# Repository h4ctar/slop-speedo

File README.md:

# slop-speedo

A custom digital speedometer/clock gauge for a motorcycle, replacing the stock
analog instrument: an X27.168 air-core stepper drives the needle, a small
OLED shows the display functions, and one MODE button drives the whole UI.
Built on an STM32F103C8T6 ("Blue Pill" class), a custom KiCad PCB, and a
hall-effect sensor off the stock speedo drive on the front wheel.

## Repo layout

- `firmware/` — STM32CubeMX + HAL project (CMake). Hand-written application
  code in `firmware/app/`; architecture in [`firmware/DESIGN.md`](firmware/DESIGN.md);
  style in [`firmware/CODE_STYLE.md`](firmware/CODE_STYLE.md).
- `hardware/` — KiCad 10 PCB project (revision 1, built and working). Generated
  outputs land in `hardware/generated/` and `hardware/JLCPCB/` via CI.

## Features

Working:

- Needle homing and positioning (X27.168, 960 steps full scale, 1.2 ms/step)
- OLED functions cycled by short MODE presses, each introduced by its name
- CLOCK: live time, long press enters set mode (set hours/minutes by button);
  the set time survives resets
- VOLT: battery voltage from the on-board divider (PA7)

In progress:

- SPEED: needle + display from the stock speedo drive (hall sensor on order);
  km/h <-> mi/h toggle
- ODOMETER / TRIP: distance from the wheel pulses; odometer persisted in
  flash, trip reset by long press

## The board

- STM32F103C8T6 (LQFP48), HSE 16 MHz, RTC on the 32.768 kHz LSE
  crystal (kept running by the J5 Vbat battery)
- Connectors: J1 debug (SWD + 3.3V), J2 mode button, J3 speedo sensor,
  J4 power (12 V -> buck 5 V -> LDO 3.3 V), J5 VBAT (backup battery),
  J7 breakout (3.3V / PA8-PA12 / GND)

## Building the firmware

Needs `arm-none-eabi-gcc`, `arm-none-eabi-newlib` (for `nano.specs`) and
`ninja` (Arch: `pacman -S arm-none-eabi-gcc arm-none-eabi-newlib ninja`).

```sh
cd firmware
cmake --preset Debug && cmake --build --preset Debug   # or Release
```

`firmware/check.sh` runs a strict (`-Werror`) build of both presets — the
same thing CI does. Output: `build/<preset>/speedo-code.elf`.

## Flashing

With an ST-Link attached:

```sh
firmware/flash.sh [Debug|Release]   # OpenOCD; defaults to Debug
```

## Using the gauge

- **Short press** cycles the display functions: SPEED -> CLOCK -> VOLT ->
  ODO -> TRIP (each function's name flashes for a second first)
- **Long press** is the current function's action: CLOCK enters set mode
  (short presses increment, long presses advance hours -> minutes -> done),
  SPEED switches km/h <-> mi/h, TRIP resets (planned)

## Development process

Work items and status live in [`TODO.md`](TODO.md). Firmware changes are
verified with `check.sh`, reviewed by the `firmware-reviewer` and
`style-reviewer` agents, and hardware-tested before being committed. CI
builds the firmware and runs KiBot (ERC/DRC + outputs) on every push.

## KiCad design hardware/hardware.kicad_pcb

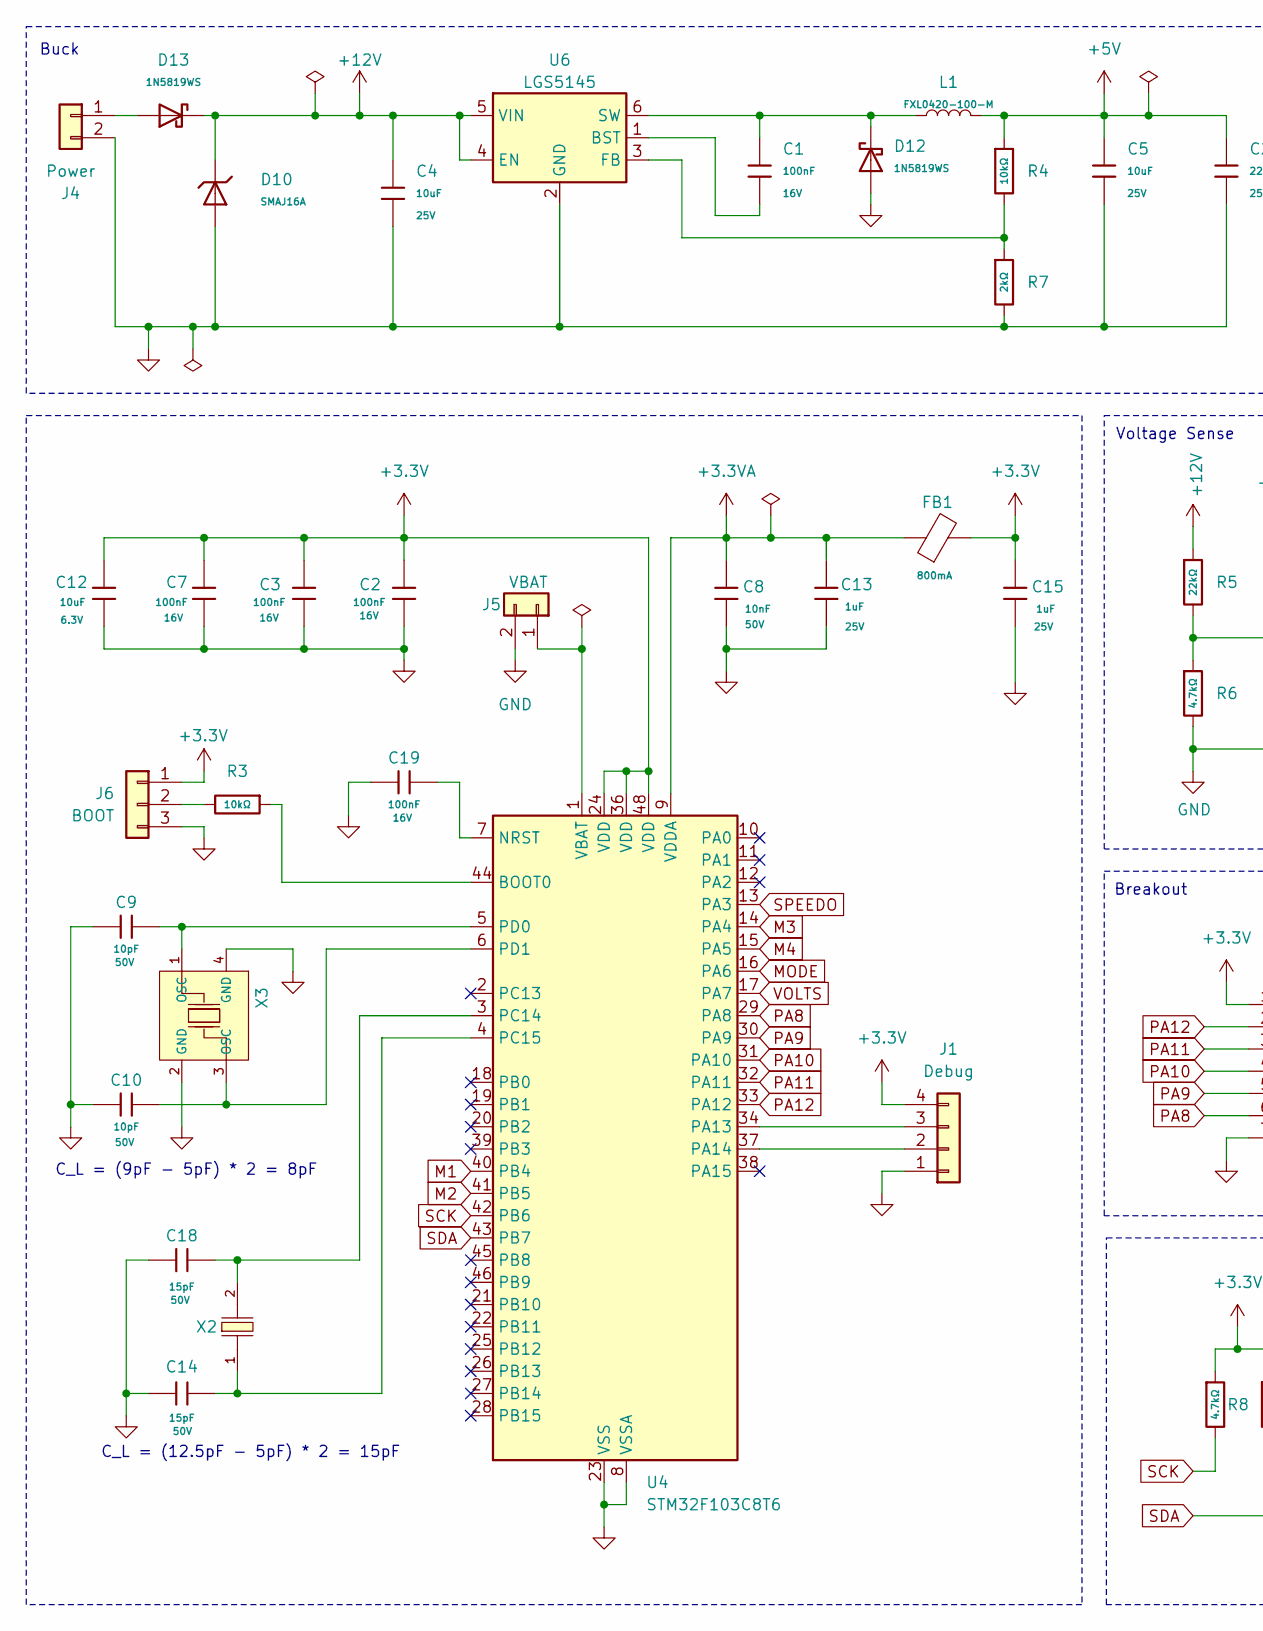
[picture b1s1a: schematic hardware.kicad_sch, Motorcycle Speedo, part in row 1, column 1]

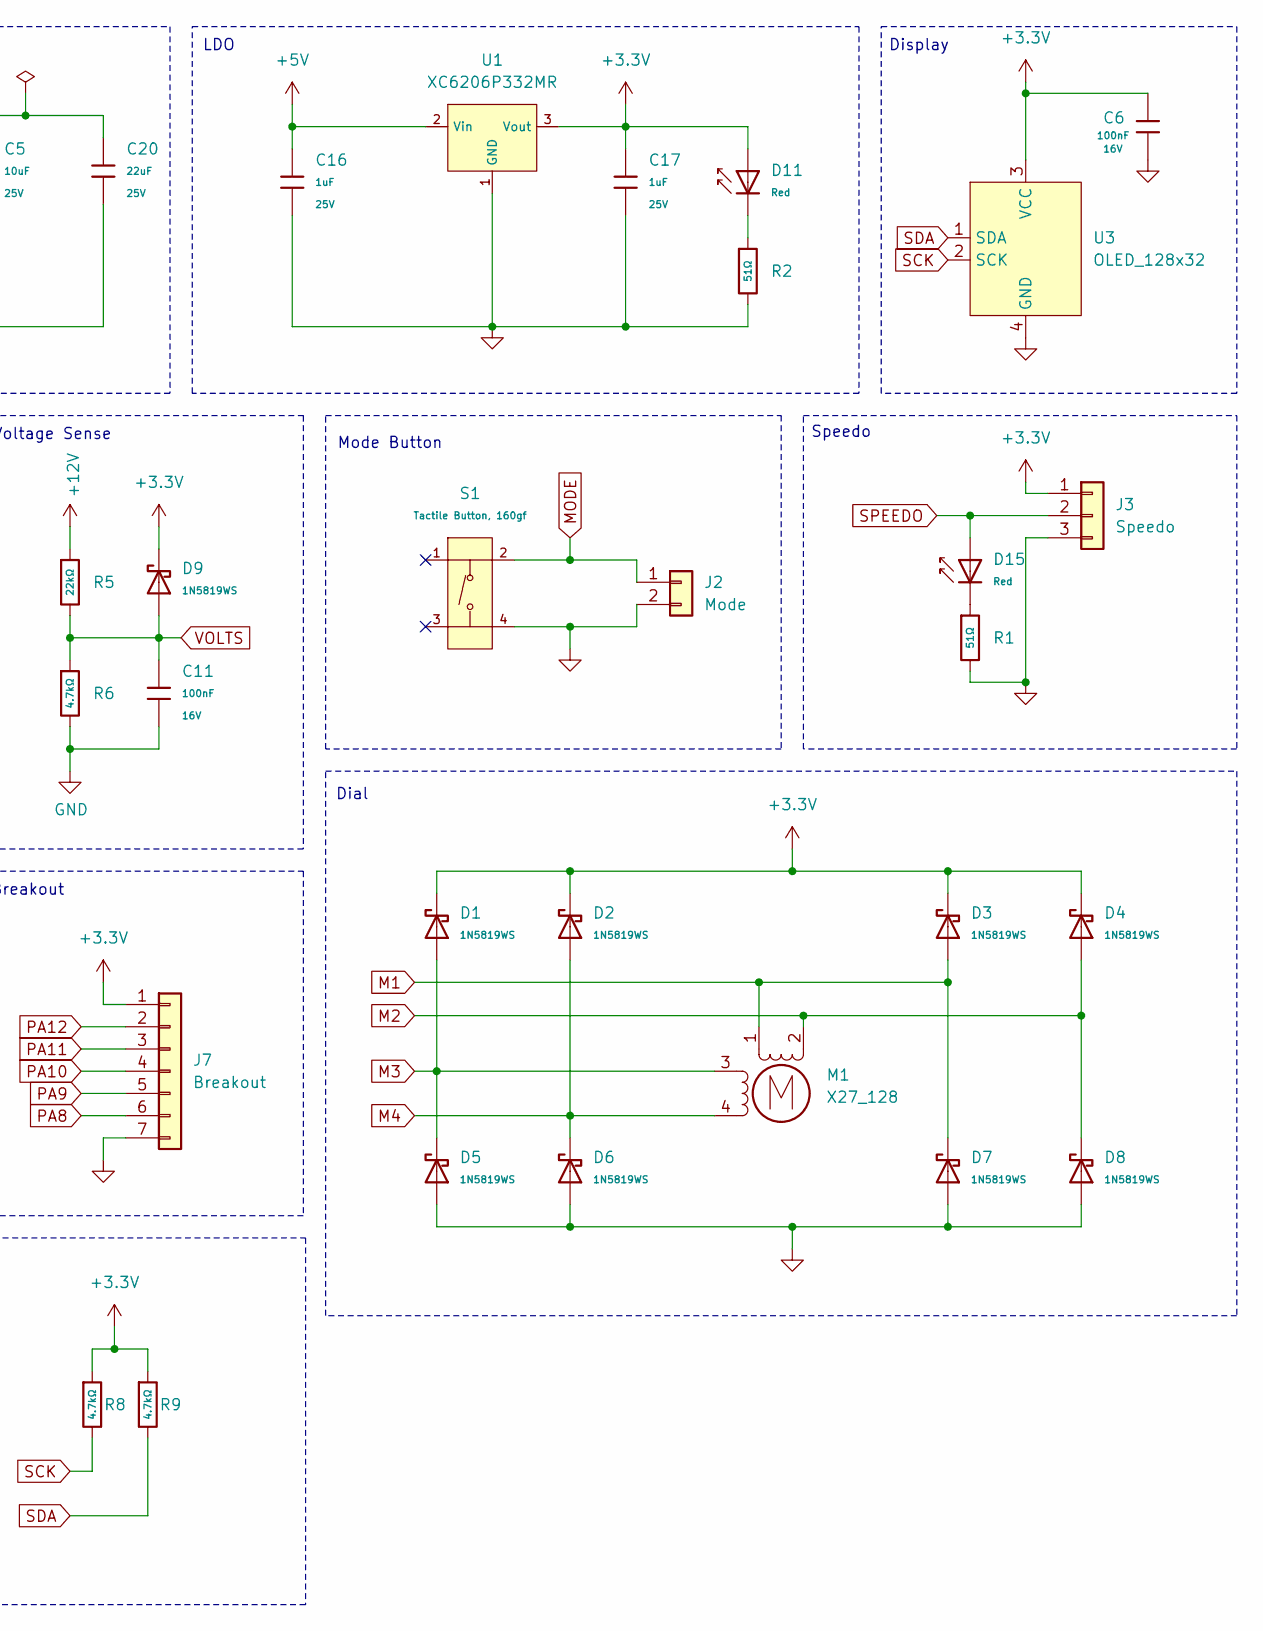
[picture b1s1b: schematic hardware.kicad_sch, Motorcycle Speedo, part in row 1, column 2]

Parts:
C1, C2, C3, C6, C7, C11, C19: 100nF; C_0402; Voltage Rated 16V; Tolerance ±10%; Part CL05B104KO5NNNC; LCSC C1525
C4, C5: 10uF; C_0805; Voltage Rated 25V; Tolerance ±10%; Part CL21A106KAYNNNE; LCSC C15850
C8: 10nF; C_0402; Voltage Rated 50V; Tolerance ±10%; Part CL05B103KB5NNNC; LCSC C15195
C9, C10: 10pF; C_0402; Voltage Rated 50V; Tolerance ±5%; Part CL05C100JB5NNNC; LCSC C32949
C12: 10uF; C_0402; Voltage Rated 6.3V; Tolerance ±20%; Part CL05A106MQ5NUNC; LCSC C15525
C13, C15, C16, C17: 1uF; C_0402; Voltage Rated 25V; Tolerance ±10%; Part CL05A105KA5NQNC; LCSC C52923
C14, C18: 15pF; C_0402; Voltage Rated 50V; Tolerance ±5%; Part 0402CG150J500NT; LCSC C1548
C20: 22uF; C_0805; Voltage Rated 25V; Tolerance ±20%; Part CL21A226MAQNNNE; LCSC C45783
D1, D2, D3, D4, D5, D6, D7, D8, D9, D12, D13: 1N5819WS; D_SOD-323; Forward Voltage (Vf@If) 600mV@1A; Reverse Voltage (Vr) 40V; Part 1N5819WS; LCSC C191023
D10: SMAJ16A; D_SMA; Breakdown Voltage 19.7V; Part SMAJ16A; LCSC C41376405
D11, D15: Red; D_0603; Part KT-0603R; LCSC C2286
FB1: FB_0805; Current Rating 800mA; Tolerance ±25%; Part GZ2012D101TF; LCSC C1015
J1: Debug; PinHeader_1x04_P2.54mm_Vertical
J2: Mode; JST_PH_B2B-PH-K_1x02_P2.00mm_Vertical
J3: Speedo; JST_PH_B3B-PH-K_1x03_P2.00mm_Vertical
J4: Power; JST_PH_B2B-PH-K_1x02_P2.00mm_Vertical
J5: VBAT; JST_PH_B2B-PH-K_1x02_P2.00mm_Vertical
J6: BOOT; PinHeader_1x03_P2.54mm_Vertical
J7: Breakout; PinSocket_1x07_P2.54mm_Vertical
L1: FXL0420-100-M; L_Sunlord_MWSA0402S; LCSC C177242
M1: X27_128; X27_168
R1, R2: 51Ω; R_0402; Overload Voltage (Max) 50V; Tolerance ±1%; Part 0402WGF510JTCE; LCSC C25125
R3, R4: 10kΩ; R_0402; Overload Voltage (Max) 50V; Tolerance ±1%; Part 0402WGF1002TCE; LCSC C25744
R5: 22kΩ; R_0402; Overload Voltage (Max) 50V; Tolerance ±1%; Part 0402WGF2202TCE; LCSC C25768
R6, R8, R9: 4.7kΩ; R_0402; Overload Voltage (Max) 50V; Tolerance ±1%; Part 0402WGF4701TCE; LCSC C25900
R7: 2kΩ; R_0402; Overload Voltage (Max) 50V; Tolerance ±1%; Part 0402WGF2001TCE; LCSC C4109
S1: Tactile Button, 160gf; SW-SMD_4P-L5.1-W5.1-P3.70-LS6.5-TL-2; Voltage Rating (Dc) 12V; Part TS-1187A-B-A-B; LCSC C318884
U1: XC6206P332MR; SOT-23-3_L2.9-W1.6-P1.90-LS2.8-BR; Output Voltage 3.3V; Dropout Voltage 680mV@(100mA); Part XC6206P332MR-G; LCSC C5446
U3: OLED_128x32; OLED_128_32
U4: STM32F103C8T6; LQFP-48_7x7mm_P0.5mm; Operating Voltage Range 2V~3.6V; Low Voltage Detection T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 2V~3.6V; Part STM32F103C8T6; LCSC C8734
U6: LGS5145; SOT-23-6; LCSC C5123971
X2: Q13FC1350000400; FC-135R_L3.2-W1.5; Frequency Tolerance ±20ppm; Part Q13FC13500004; LCSC C32346
X3: X322516MLB4SI; OSC-SMD_4P-L3.2-W2.5-BL; Frequency Tolerance ±10ppm; Part X322516MLB4SI; LCSC C13738

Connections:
+3.3V: C2.1, C3.1, C6.1, C7.1, C12.1, C15.1, C17.1, D1.1, D2.1, D3.1, D4.1, D9.1, D11.2, FB1.2, J1.4, J3.1, J6.1, J7.1, R8.1, R9.1, U1.3 (Vout), U3.3 (VCC), U4.24 (VDD), U4.36 (VDD), U4.48 (VDD)
+3.3VA: C8.1, C13.1, FB1.1, U4.9 (VDDA)
+5V: C5.1, C16.1, C20.1, L1.2, R4.1, U1.2 (Vin)
+12V: C4.1, D10.1, D13.1, R5.1, U6.4 (EN), U6.5 (VIN)
GND: C2.2, C3.2, C4.2, C5.2, C6.2, C7.2, C8.2, C9.1, C10.1, C11.2, C12.2, C13.2, C14.1, C15.2, C16.2, C17.2, C18.1, C19.1, C20.2, D5.2, D6.2, D7.2, D8.2, D10.2, D12.2, J1.1, J2.2, J3.3, J4.2, J5.2, J6.3, J7.7, R1.2, R2.2, R6.2, R7.2, S1.4 (D), U1.1 (GND), U3.4 (GND), U4.8 (VSSA), U4.23 (VSS), U4.35 (VSS), U4.47 (VSS), U6.2 (GND), X3.2 (GND), X3.4 (GND)
M1: D3.2, D7.1, M1.1, U4.40 (PB4)
M2: D4.2, D8.1, M1.2 (-), U4.41 (PB5)
M3: D1.2, D5.1, M1.3, U4.14 (PA4)
M4: D2.2, D6.1, M1.4, U4.15 (PA5)
MODE: J2.1, S1.2 (B), U4.16 (PA6)
unnamed: D11.1, R2.1
unnamed: D15.1, R1.1
unnamed: J1.2, U4.37 (PA14)
unnamed: J1.3, U4.34 (PA13)
unnamed: D13.2, J4.1
unnamed: J5.1, U4.1 (VBAT)
unnamed: J6.2, R3.2
unnamed: R3.1, U4.44 (BOOT0)
unnamed: C19.2, U4.7 (NRST)
unnamed: C18.2, U4.3 (PC14), X2.2
unnamed: C14.2, U4.4 (PC15), X2.1
unnamed: C9.2, U4.5 (PD0), X3.1 (OSC)
unnamed: C10.2, U4.6 (PD1), X3.3 (OSC)
unnamed: C1.1, U6.1 (BST)
unnamed: R4.2, R7.1, U6.3 (FB)
unnamed: C1.2, D12.1, L1.1, U6.6 (SW)
PA8: J7.6, U4.29 (PA8)
PA9: J7.5, U4.30 (PA9)
PA10: J7.4, U4.31 (PA10)
PA11: J7.3, U4.32 (PA11)
PA12: J7.2, U4.33 (PA12)
SCK: R8.2, U3.2 (SCK), U4.42 (PB6)
SDA: R9.2, U3.1 (SDA), U4.43 (PB7)
SPEEDO: D15.2, J3.2, U4.13 (PA3)
VOLTS: C11.1, D9.2, R5.2, R6.1, U4.17 (PA7)

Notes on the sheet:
LDO
Dial
Speedo
C_L = (9pF - 5pF) * 2 = 8pF
C_L = (12.5pF - 5pF) * 2 = 15pF
Display
Buck
Breakout
Mode Button
Voltage Sense

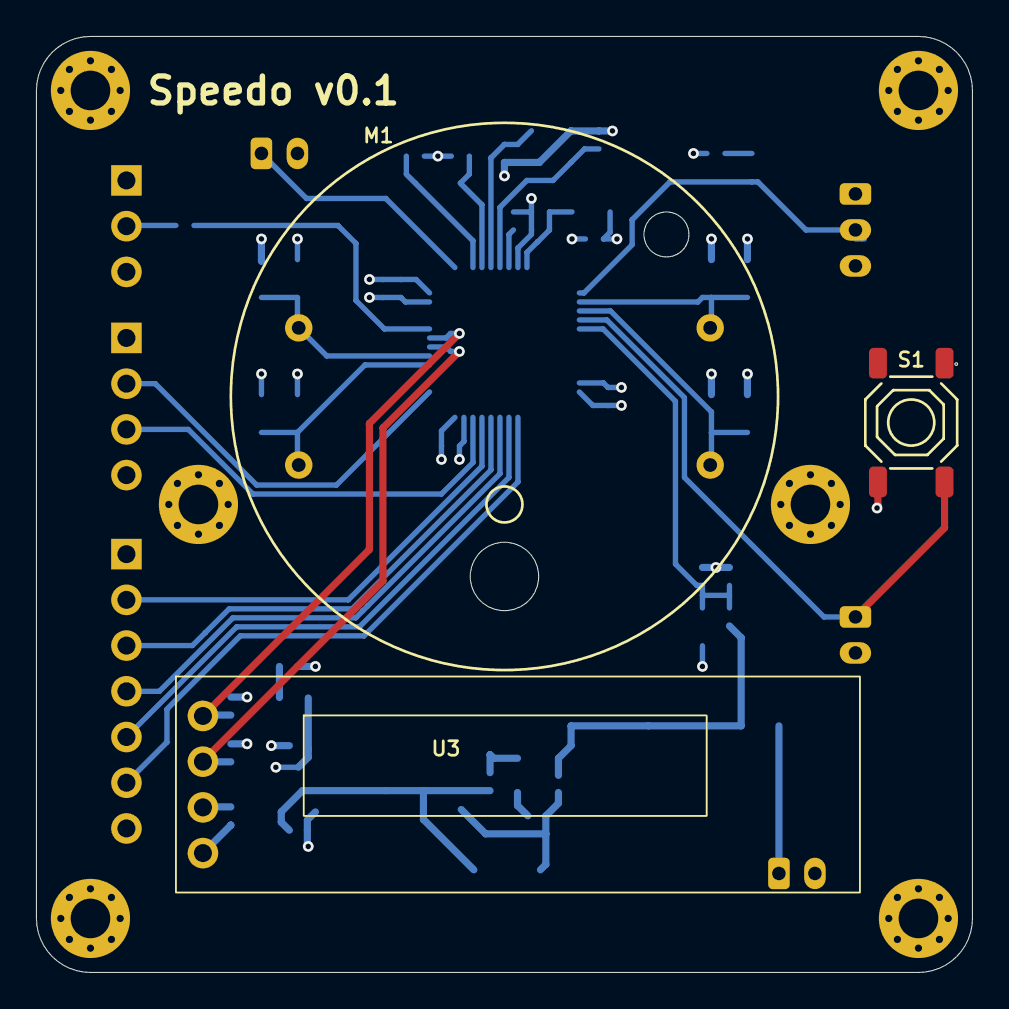
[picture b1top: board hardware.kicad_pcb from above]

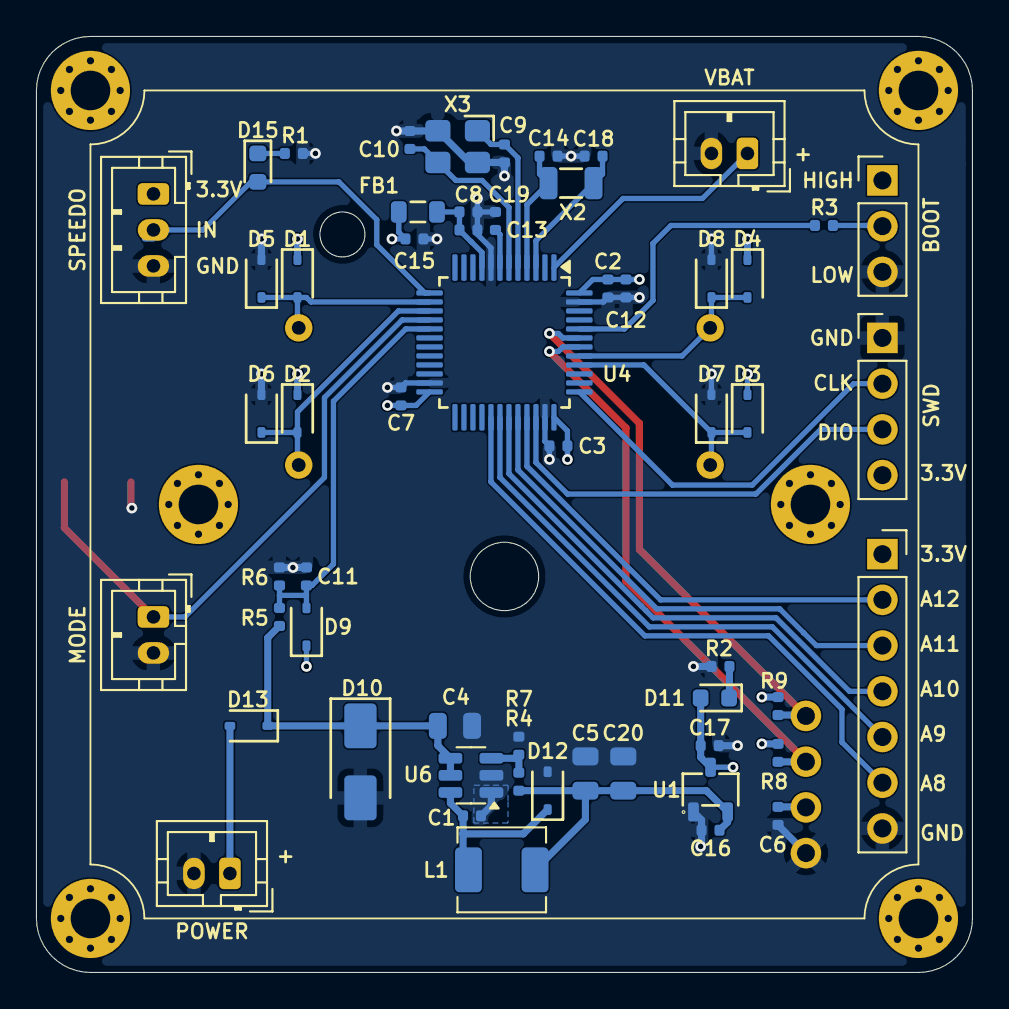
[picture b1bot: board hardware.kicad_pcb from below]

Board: 4 copper layers, 52.0 x 52.0 mm, 66 parts (57 on the bottom side), 35 nets.

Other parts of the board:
H1, H2, H3, H4, H5, H6: MountingHole_2.2mm_M2_Pad_Via

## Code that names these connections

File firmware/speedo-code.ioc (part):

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Mcu.Name=STM32F103C(8-B)Tx
Mcu.Package=LQFP48
Mcu.UserName=STM32F103C8Tx
PA13.Mode=Serial_Wire
PA13.Signal=SYS_JTMS-SWDIO
PA14.Mode=Serial_Wire
PA14.Signal=SYS_JTCK-SWCLK
PA4.GPIOParameters=GPIO_Label
PA4.GPIO_Label=M3
PA4.Signal=GPIO_Output
PA5.GPIOParameters=GPIO_Label
PA5.GPIO_Label=M4
PA5.Signal=GPIO_Output
PA6.GPIOParameters=GPIO_PuPd
PA6.GPIO_PuPd=GPIO_PULLUP
PA6.Signal=GPIO_Input
PA7.GPIOParameters=GPIO_Label
PA7.GPIO_Label=VOLTS
PA7.Signal=ADCx_IN7
PB4.GPIOParameters=GPIO_Label
PB4.GPIO_Label=M1
PB4.Signal=GPIO_Output
PB5.GPIOParameters=GPIO_Label
PB5.GPIO_Label=M2
PB5.Signal=GPIO_Output
PB6.Mode=I2C
PB6.Signal=I2C1_SCL
PB7.Mode=I2C
PB7.Signal=I2C1_SDA
PC14-OSC32_IN.Mode=LSE-External-Oscillator
PC14-OSC32_IN.Signal=RCC_OSC32_IN
PC15-OSC32_OUT.Mode=LSE-External-Oscillator
PC15-OSC32_OUT.Signal=RCC_OSC32_OUT
PD0-OSC_IN.Mode=HSE-External-Oscillator
PD0-OSC_IN.Signal=RCC_OSC_IN
PD1-OSC_OUT.Mode=HSE-External-Oscillator
PD1-OSC_OUT.Signal=RCC_OSC_OUT
RCC.HSE_VALUE=16000000
RCC.SYSCLKFreq_VALUE=32000000
RCC.SYSCLKSource=RCC_SYSCLKSOURCE_PLLCLK
board=custom
